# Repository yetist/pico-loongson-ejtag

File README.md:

# Pico Loongson EJTAG

[ENGLISH](README.en.md)

降成本版新款点这里 >> [CH32 Loongson EJTAG](https://github.com/RigoLigoRLC/ch32-loongson-ejtag)

欢迎加入！本项目专为龙芯嵌入式开发者爱好者打造，旨在重新实现龙芯官方EJTAG仿真器的核心功能，力求实现硬件功能完全对标且上位机软件兼容互通。

作为龙芯生态的共建者，我们深知龙芯3A6000等桌面级处理器性能比较亮眼，但其整机体积大、价格门槛高、与海外顶尖产品尚存差距的现状，让不少开发者望而却步（包括笔者本人）。而2K0300开发板的问世彻底改变了这一局面——这颗SoC不仅拥有媲美（超越）iMX6ULL等主流芯片的CoreMark性能，支持跑Linux/裸机，更以价格（百元级开发板）和小巧体积，为开发者打开了低成本进入LoongArch世界的通道。

然而，对于专注于裸机开发的嵌入式开发者而言，现有生态仍存在痛点：虽然2K0300可运行裸机程序，但官方调试工具高昂的售价成为了拦路虎。长期以来，龙芯的主要业务集中在桌面领域，对嵌入式生态投入有限（2K0300至今仅有第三方提供的残缺SDK，其IDE更是近乎讽刺地仅支持Windows平台）。我们希望通过这个项目证明：嵌入式开发者完全有能力为LoongArch的嵌入式开放生态开辟道路。

当前，固件基于逆向工程成果，主要参考对象为搭载20210129版本FPGA固件的官方调试工具和`la_dbg_tool_usb.exe`工具，并基于此独立实现了设备与上位机的通信协议、JTAG驱动。

## 功能完整度

当前版本还未完整实现所有命令的执行，会导致部分调试功能无法使用：

- 0xe，0xf：快速读内存指令

  将导致批量读取内存不可用

部分功能未完整验证，可能在部分机器上工作异常：

- 0xc，0xd：快速写内存指令

  未在 2K0300 以外的机器上测试，多核心处理器的适应性不明。仅在 2K0300 上测试了 SPI Flash 烧写功能。

## 实现方案

本固件基于树莓派RP2040-Zero开发板（成本极低，轻松复刻），具体引脚定义如下：

| RP2040 GPIO编号 | JTAG信号  | 备注 |
|----------------|----------|-----|
| 8              | #TRST    |     |
| 9              | TDI      |     |
| 10             | TDO      |     |
| 11             | TMS      |     |
| 12             | TCK      |     |
| 13             | #BRST    |     |
| 14             | #DINT    |     |
| 26             | VIO      | 模拟引脚 |

板载WS2812（GPIO16控制）作为状态指示灯，GPIO0/1上的UART0接口可输出开发调试信息。

- `src/lsejtag`与`inc/lsejtag`目录封装了与平台无关的核心逻辑（内部称其为`LS-EJTAG`协议栈，但并没有独立发布），负责处理上位机指令解析
- `src/ejtag_impl.c`包含硬件平台相关代码，移植至其他主控芯片时需重新实现

我们正在酝酿基于HPM5301主控的升级方案（硬件设计采用OSL-W-2.0协议开源，固件遵循GPL-3.0协议），重点是利用它的高速USB以图加快速度，敬请期待！

# 构建指南

我个人因为并不想安装体积比较大的SDK安装包，基于Windows环境手搓了构建流程，请按以下步骤配置开发环境：

## picotool安装
请将`picotool`完整安装至`C:\Program Files\CMake\picotool\`目录（内含CMake目标文件等必要组件）。`pioasm`工具也需同步安装。

**替代方案**：将安装目录路径添加至`CMAKE_PREFIX_PATH`环境变量，具体方式可依个人偏好选择。

## 环境配置
- `PICO_SDK_BASE`：设置为pico-sdk仓库的本地克隆路径（直接指向仓库根目录）
- `PICO_SDK_COMPILER_PATH`：指向MCU编译器所在目录（需包含`arm-none-eabi-gcc.exe`等可执行文件）

## VSCode编译流程
1. 通过Workspace Settings配置上述环境变量
2. 启动构建时选择"ARM GCC (Pico)"工具链
3. 正常情况下即可完成编译，若遇异常...祝君调试愉快

## clangd适配
因clangd/LLVM的设计缺陷（详见clangd/clangd#2289），需在clangd参数中添加：`--query-driver=.../your/gnu/toolchain/bin/arm-none-eabi-*.exe`以强制clangd识别GNU工具链路径（否则会误判为LLVM工具链导致头文件搜索失败）

# 许可

本项目除引用了其他项目有明确版权标识的文件之外，其他的代码均以 GPL-3.0-only 许可证发布。

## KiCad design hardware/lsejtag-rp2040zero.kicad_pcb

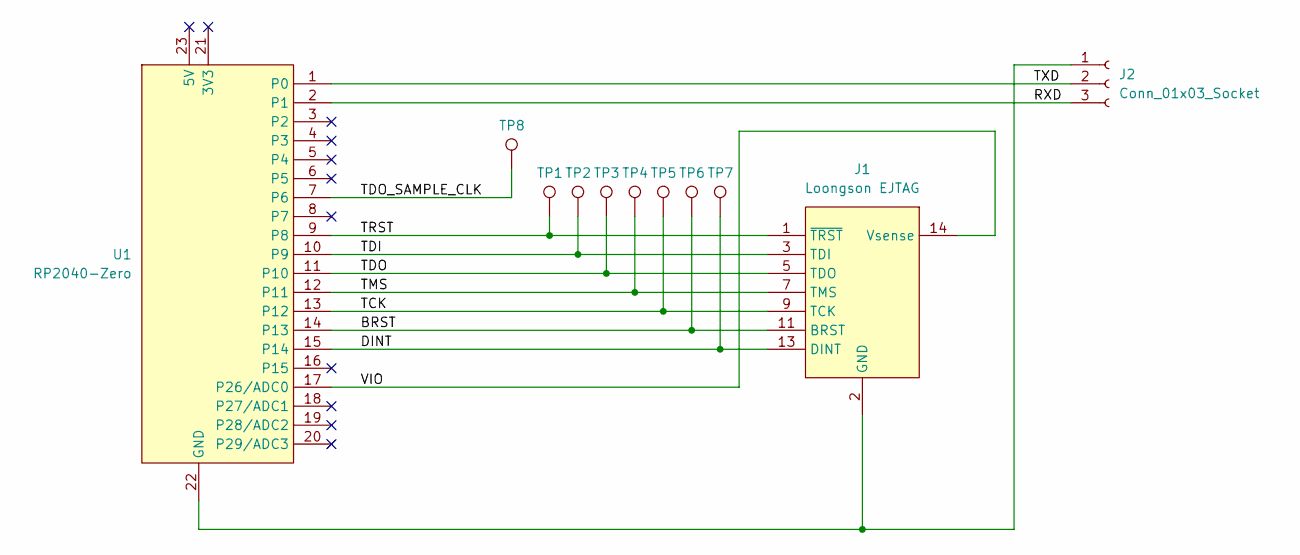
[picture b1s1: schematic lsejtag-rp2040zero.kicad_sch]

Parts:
J1: Loongson EJTAG; IDC-Header_2x07_P2.54mm_Vertical
J2: Conn_01x03_Socket; PinHeader_1x03_P2.54mm_Vertical
TP1, TP2, TP3, TP4, TP5, TP6, TP7, TP8: TestPoint; PinHeader_1x01_P2.54mm_Vertical
U1: RP2040-Zero

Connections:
/BRST: J1.11 (BRST), TP6.1, U1.14 (P13)
/DINT: J1.13 (DINT), TP7.1, U1.15 (P14)
/RXD: J2.3, U1.2 (P1)
/TCK: J1.9 (TCK), TP5.1, U1.13 (P12)
/TDI: J1.3 (TDI), TP2.1, U1.10 (P9)
/TDO: J1.5 (TDO), TP3.1, U1.11 (P10)
/TDO_SAMPLE_CLK: TP8.1, U1.7 (P6)
/TMS: J1.7 (TMS), TP4.1, U1.12 (P11)
/TRST: J1.1 (~TRST), TP1.1, U1.9 (P8)
/TXD: J2.2, U1.1 (P0)
/VIO: J1.14 (Vsense), U1.17 (P26/ADC0)
GND: J1.2 (GND), J1.4 (GND), J1.6 (GND), J1.8 (GND), J1.10 (GND), J2.1, U1.22 (GND)

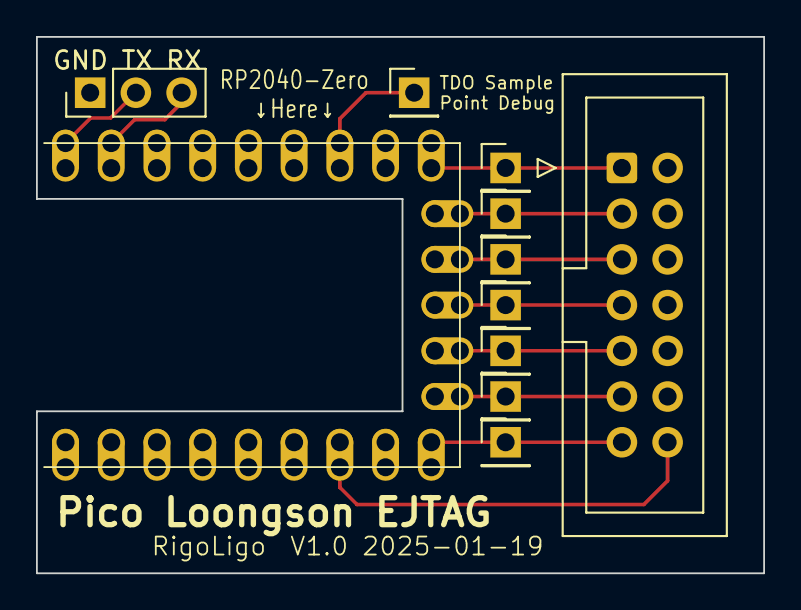
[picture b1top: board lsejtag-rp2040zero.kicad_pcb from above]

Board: 2 copper layers, 40.4 x 29.8 mm, 11 parts (0 on the bottom side), 12 nets.

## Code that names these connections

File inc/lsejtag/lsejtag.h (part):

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    io_led,                 // Green LED. Default to low.
    io_fpga_reset,          // Non-used.
    io_oe,                  // JTAG output enable. When OE is low output is enabled. Default to low.
    io_trst,                // TRST pin. Default to high.
    io_brst,                // BRST pin. Default to high.
    io_dint,                // DINT pin. Default to high.
    io_tap_reset,           // Non-used.
    io_maximum,
} lsejtag_io;
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
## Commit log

2025-01-18 feat: PIO logic verified
2025-01-27 feat: Basic IR/DR R/W funcionality implemented
2025-01-28 feat: reconfigure JTAG frequency
2025-01-28 chore: update README
2025-01-28 feat: PCB design
2025-02-03 feat: Implemented Fast Write (for flashing) NOT FULLY VERIFIED
2025-02-03 chore: bump to version 0.2.0
2025-02-03 Add ci to produce binaries
2025-02-03 fix: change default IR params to MIPS style
2025-06-21 chore: Update README.md about CH32 version
2025-06-21 chore: Update README.en.md about CH32 version
2025-07-20 add pcb
